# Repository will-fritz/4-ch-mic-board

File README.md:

# 4-ch-mic-board
4 ch microphone board to replace seed studio 6 ch microphone board stack

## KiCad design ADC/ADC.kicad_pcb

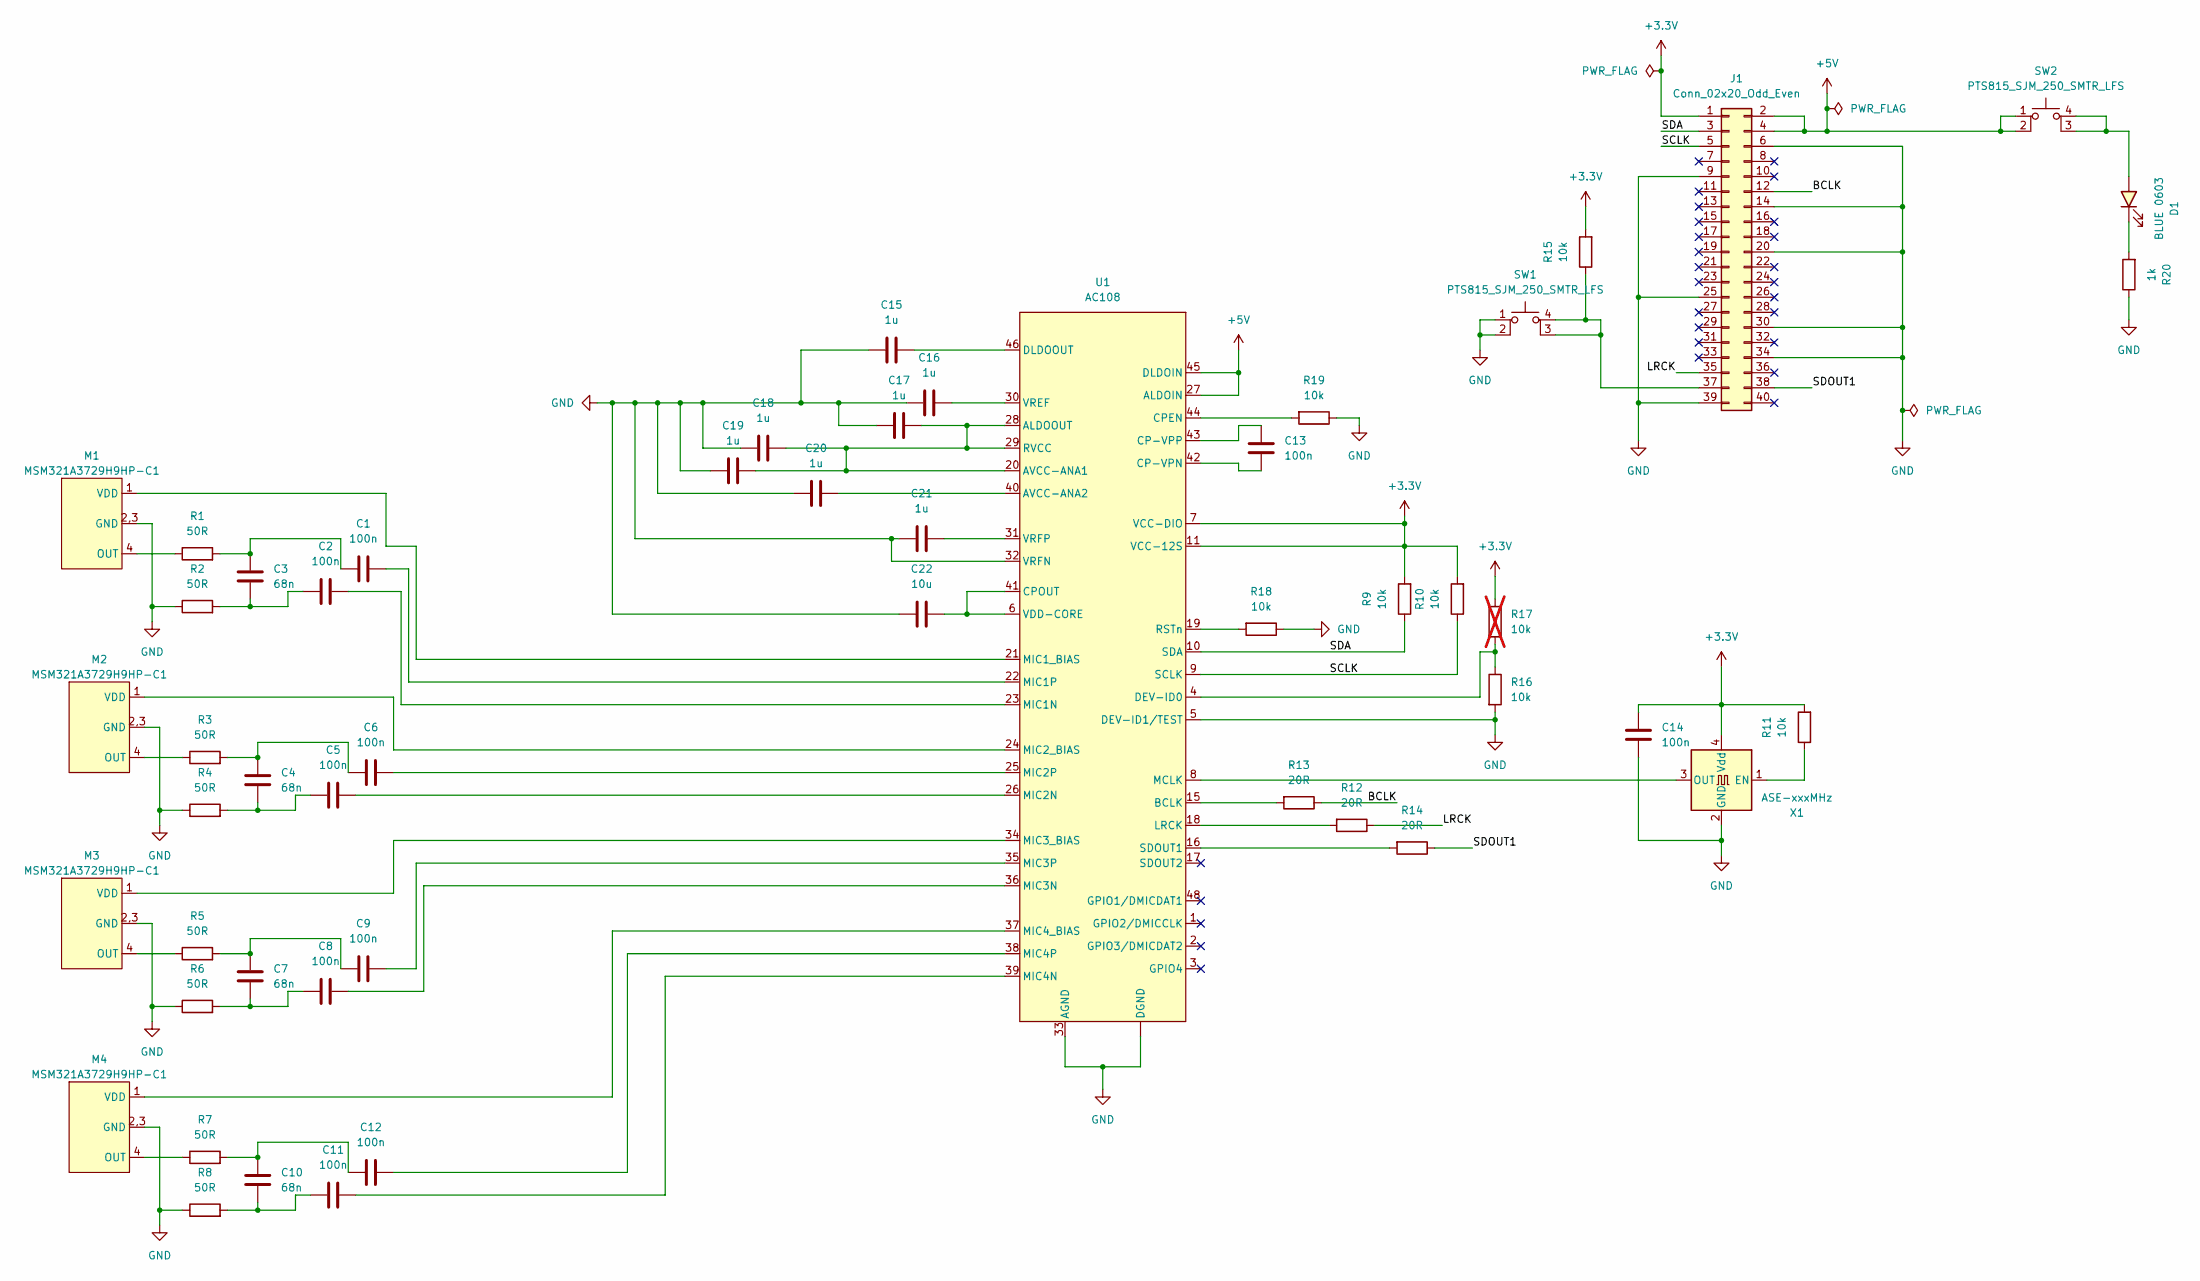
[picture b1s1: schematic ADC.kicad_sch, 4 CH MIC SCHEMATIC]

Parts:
C1, C2, C5, C6, C8, C9, C11, C12, C13, C14: 100n; C_0603_1608Metric
C3, C4, C7, C10: 68n; C_0603_1608Metric
C15, C16, C17, C18, C19, C20, C21: 1u; C_0603_1608Metric
C22: 10u; C_0603_1608Metric
D1: BLUE 0603; LED_0603_1608Metric; MPN EAST16084BA0
J1: Conn_02x20_Odd_Even; PinSocket_2x20_P2.54mm_Vertical
M1, M2, M3, M4: MSM321A3729H9HP-C1; MSM321A3729H8HP-C_FP
R1, R2, R3, R4, R5, R6, R7, R8: 50R; R_0603_1608Metric
R9, R10, R11, R15, R16, R18, R19: 10k; R_0603_1608Metric
R12, R13, R14: 20R; R_0603_1608Metric
R17: 10k; R_0603_1608Metric; not fitted
R20: 1k; R_0603_1608Metric
SW1, SW2: PTS815_SJM_250_SMTR_LFS; MPN PTS815 SJM 250 SMTR LFS
U1: AC108
X1: ASE-xxxMHz; Oscillator_SMD_Abracon_ASE-4Pin_3.2x2.5mm

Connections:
+3.3V: C14.2, J1.1, R9.2, R10.2, R11.2, R15.2, R17.1, U1.7 (VCC-DIO), U1.11 (VCC-12S), X1.4 (Vdd)
+5V: J1.2, J1.4, SW2.1, SW2.2, U1.27 (ALDOIN), U1.45 (DLDOIN)
/BCLK: J1.12, R13.1
/LRCK: J1.35, R12.1
/SCLK: J1.5, R10.1, U1.9 (SCLK)
/SDA: J1.3, R9.1, U1.10 (SDA)
/SDOUT1: J1.38, R14.1
GND: C14.1, C15.1, C16.1, C17.1, C18.1, C19.1, C20.1, C21.1, C22.1, J1.6, J1.9, J1.14, J1.20, J1.25, J1.30, J1.34, J1.39, M1.2, M1.2,3 (GND), M1.3, M2.2, M2.2,3 (GND), M2.3, M3.2, M3.2,3 (GND), M3.3, M4.2, M4.2,3 (GND), M4.3, R2.1, R4.1, R6.1, R8.1, R16.2, R18.1, R19.1, R20.1, SW1.1, SW1.2, U1. (DGND), U1.5 (DEV-ID1/TEST), U1.32 (VRFN), U1.33 (AGND), X1.2 (GND)
unnamed: C1.1, C3.1, R1.2
unnamed: C2.1, C3.2, R2.2
unnamed: C4.1, C6.1, R3.2
unnamed: C4.2, C5.1, R4.2
unnamed: C7.1, C9.1, R5.2
unnamed: C7.2, C8.1, R6.2
unnamed: C10.1, C12.1, R7.2
unnamed: C10.2, C11.1, R8.2
unnamed: D1.2 (A), SW2.3 (K), SW2.4 (A)
unnamed: D1.1 (K), R20.2
unnamed: J1.37, R15.1, SW1.3 (K), SW1.4 (A)
unnamed: M1.4 (OUT), R1.1
unnamed: M1.1 (VDD), U1.21 (MIC1_BIAS)
unnamed: M2.4 (OUT), R3.1
unnamed: M2.1 (VDD), U1.24 (MIC2_BIAS)
unnamed: M3.4 (OUT), R5.1
unnamed: M3.1 (VDD), U1.34 (MIC3_BIAS)
unnamed: M4.4 (OUT), R7.1
unnamed: M4.1 (VDD), U1.37 (MIC4_BIAS)
unnamed: C17.2, C18.2, C19.2, U1.20 (AVCC-ANA1), U1.28 (ALDOOUT), U1.29 (RVCC)
unnamed: C20.2, U1.40 (AVCC-ANA2)
unnamed: R13.2, U1.15 (BCLK)
unnamed: C13.1, U1.42 (CP-VPN)
unnamed: C13.2, U1.43 (CP-VPP)
unnamed: R19.2, U1.44 (CPEN)
unnamed: C22.2, U1.6 (VDD-CORE), U1.41 (CPOUT)
unnamed: R16.1, R17.2, U1.4 (DEV-ID0)
unnamed: C15.2, U1.46 (DLDOOUT)
unnamed: R12.2, U1.18 (LRCK)
unnamed: U1.8 (MCLK), X1.3 (OUT)
unnamed: C2.2, U1.23 (MIC1N)
unnamed: C1.2, U1.22 (MIC1P)
unnamed: C5.2, U1.26 (MIC2N)
unnamed: C6.2, U1.25 (MIC2P)
unnamed: C8.2, U1.36 (MIC3N)
unnamed: C9.2, U1.35 (MIC3P)
unnamed: C11.2, U1.39 (MIC4N)
unnamed: C12.2, U1.38 (MIC4P)
unnamed: R18.2, U1.19 (RSTn)
unnamed: R14.2, U1.16 (SDOUT1)
unnamed: C16.2, U1.30 (VREF)
unnamed: C21.2, U1.31 (VRFP)
unnamed: R11.1, X1.1 (EN)

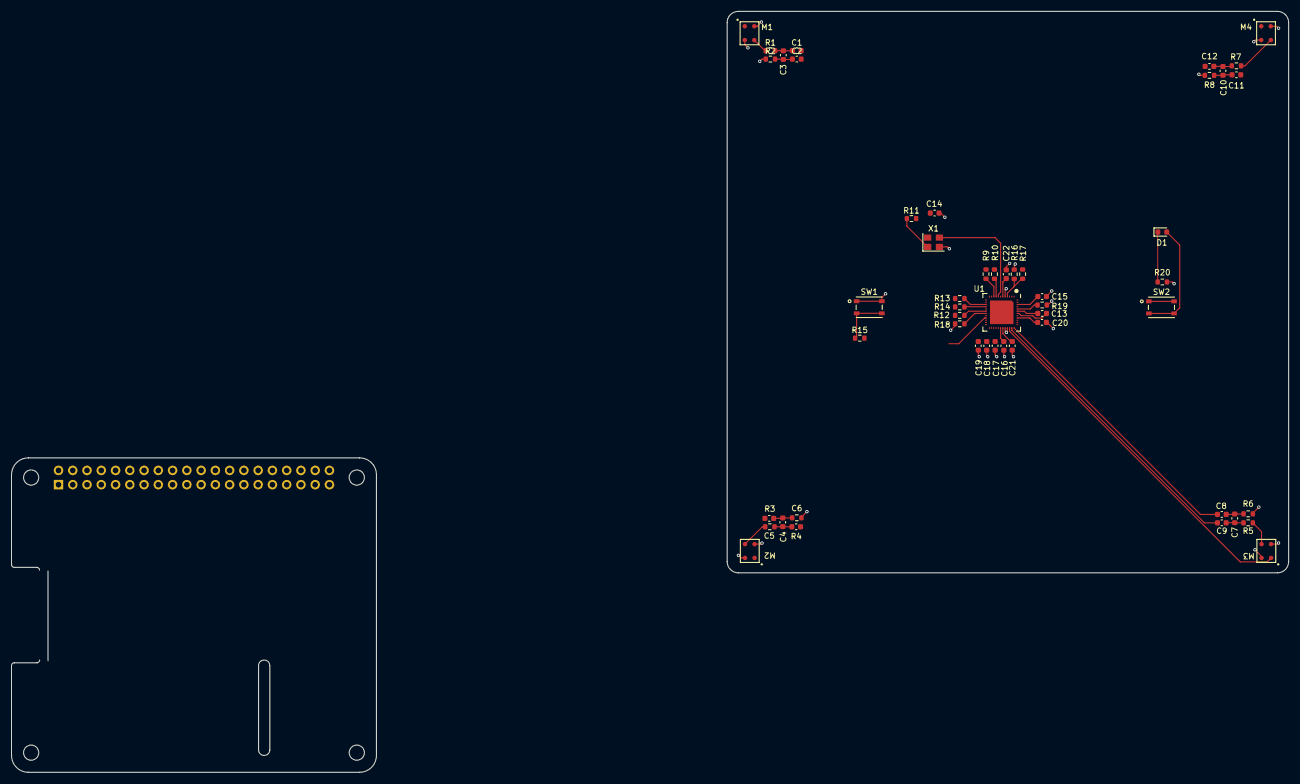
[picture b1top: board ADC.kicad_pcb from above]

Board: 4 copper layers, 227.4 x 135.5 mm, 56 parts (1 on the bottom side), 51 nets.

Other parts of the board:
MH1, MH2, MH3, MH4: MountingHole_2.7mm_M2.5

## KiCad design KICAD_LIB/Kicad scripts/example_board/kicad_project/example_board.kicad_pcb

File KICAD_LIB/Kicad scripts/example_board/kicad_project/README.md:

# KiCad project to use as demo for python scripts

## This board is intended for demo purposes only, it is not meant to be manufactured

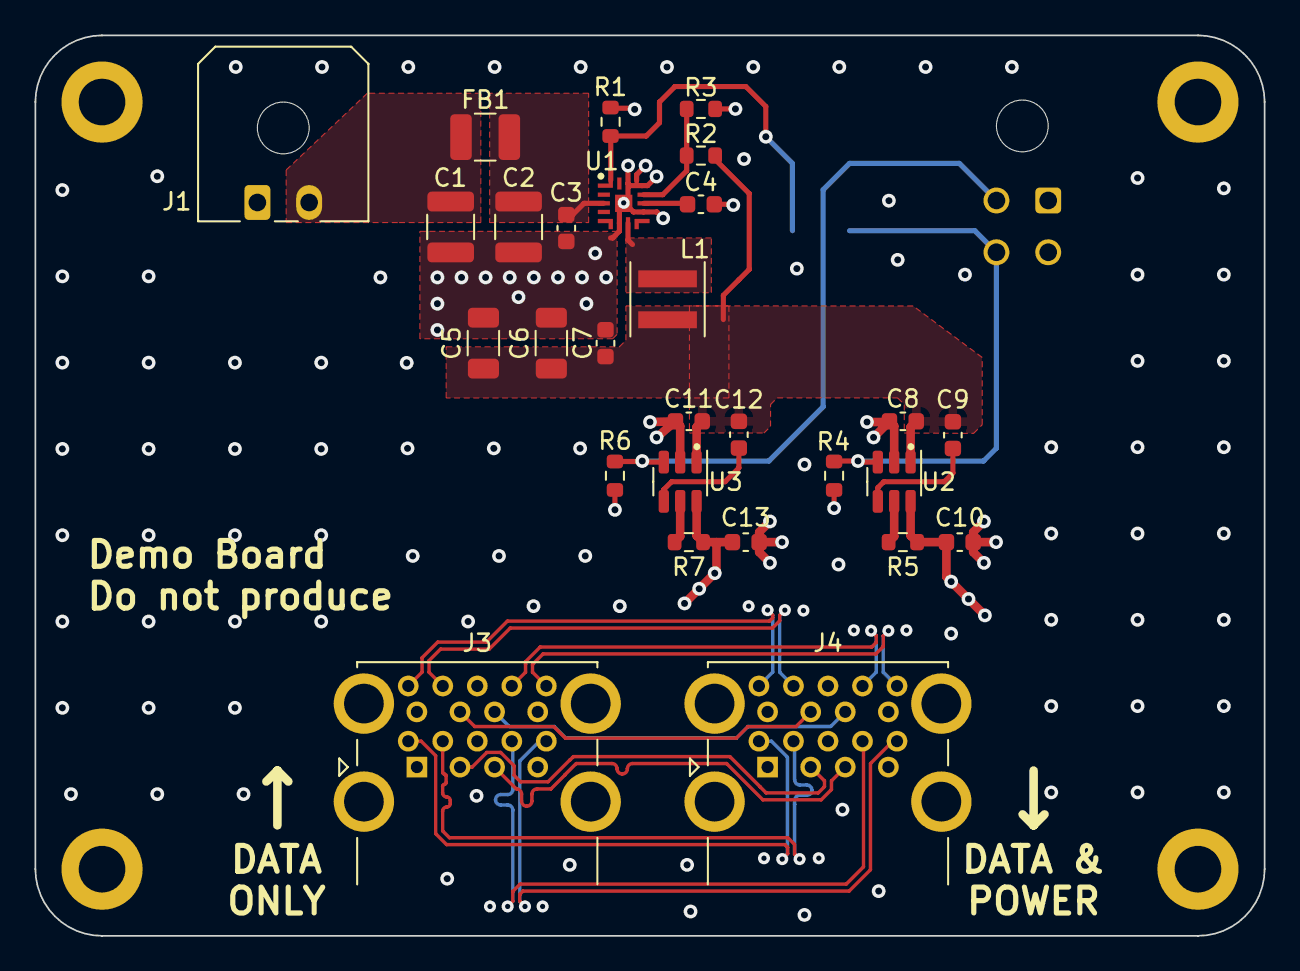
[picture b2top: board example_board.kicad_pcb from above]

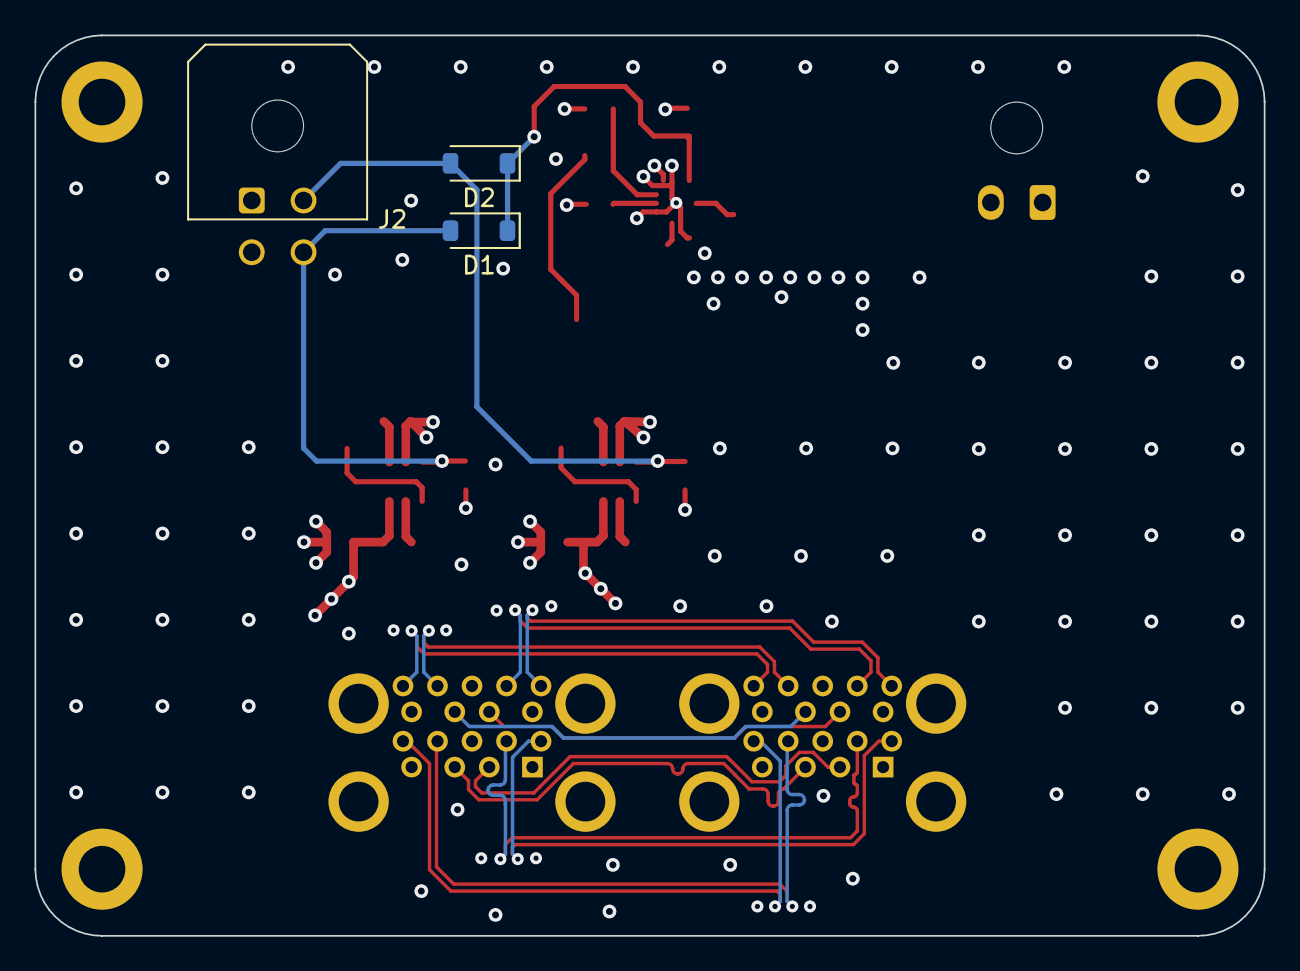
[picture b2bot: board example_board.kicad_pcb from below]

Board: 4 copper layers, 71.2 x 52.2 mm, 35 parts (3 on the bottom side), 28 nets.

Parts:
C1, C2: 10u 50V; C_1210_3225Metric
C3: 100n 50v; C_0603_1608Metric
C4, C8, C10, C11, C13: 1u 50V; C_0603_1608Metric
C5, C6: 22u 10v; C_1206_3216Metric
C7: 100n 25v; C_0603_1608Metric
C9, C12: 470p; C_0603_1608Metric
D1, D2: 1N4148W; D_SOD-123
FB1: 1k @100MHz 2A; L_1210_3225Metric
H1, H2, H3, H4: MountingHole_Pad; MountingHole_2.7mm_M2.5_DIN965_Pad
J1: micro-fit_1x2_3mm; Molex_Micro-Fit_3.0_43650-0200_1x02_P3.00mm_Horizontal
J2: micro-fit_2x2_3mm; Molex_Micro-Fit_3.0_43045-0400_2x02_P3.00mm_Horizontal
J3, J4: molex_048406-0001; USB3_A_Molex_48406-0001_Horizontal_Stacked
L1: 3u3 5A; L_Coilcraft_XxL4030
R1, R4, R6: 1M; R_0603_1608Metric
R2: 0R; R_0603_1608Metric
R3: DNF; R_0603_1608Metric
R5, R7: 10k; R_0603_1608Metric
U1: LMQ66430R5RXBR; VQFN-FCRLF14_RXB_TEX
U2, U3: TPS22917DBVx; SOT-23-6

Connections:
+5V: C5.1, C6.1, C7.1, C8.1, C9.1, C11.1, C12.1, L1.2, R2.1, U2.1 (IN), U3.1 (IN)
/USB_in/USB_btm_data.D+: J3.3 (D1+), J4.3 (D1+)
/USB_in/USB_btm_data.D-: J3.2 (D1-), J4.2 (D1-)
/USB_in/USB_btm_data.SSRX+: J3.6 (SSRX1+), J4.6 (SSRX1+)
/USB_in/USB_btm_data.SSRX-: J3.5 (SSRX1-), J4.5 (SSRX1-)
/USB_in/USB_btm_data.SSTX+: J3.9 (SSTX1+), J4.9 (SSTX1+)
/USB_in/USB_btm_data.SSTX-: J3.8 (SSTX1-), J4.8 (SSTX1-)
/USB_in/USB_top_data.D+: J3.12 (D2+), J4.12 (D2+)
/USB_in/USB_top_data.D-: J3.11 (D2-), J4.11 (D2-)
/USB_in/USB_top_data.SSRX+: J3.15 (SSRX2+), J4.15 (SSRX2+)
/USB_in/USB_top_data.SSRX-: J3.14 (SSRX2-), J4.14 (SSRX2-)
/USB_in/USB_top_data.SSTX+: J3.18 (SSTX2+), J4.18 (SSTX2+)
/USB_in/USB_top_data.SSTX-: J3.17 (SSTX2-), J4.17 (SSTX2-)
/USB_out/VBUS_BTM: C13.1, J4.1 (VBUS1), R7.1, U3.6 (OUT)
/USB_out/VBUS_TOP: C10.1, J4.10 (VBUS2), R5.1, U2.6 (OUT)
/power_ctl/FB: R2.2, R3.1, U1.11 (VOUT/FB)
/power_ctl/REG_EN: D1.1 (K), D2.1 (K), R1.1, U1.1 (EN)
/power_ctl/SW: L1.1, U1.7 (SW)
/power_ctl/VBUS_BTM_EN: D2.2 (A), J2.2, R6.1, U3.3 (ON)
/power_ctl/VBUS_TOP_EN: D1.2 (A), J2.4, R4.1, U2.3 (ON)
/power_ctl/VIN: C1.1, FB1.2, J1.2
/power_ctl/VIN_FILT: C2.1, C3.1, FB1.1, U1.3 (VIN)
GND: C1.2, C2.2, C3.2, C4.2, C5.2, C6.2, C7.2, C8.2, C10.2, C11.2, C13.2, H1.1, H2.1, H3.1, H4.1, J1.1, J2.1, J2.3, J3.4 (GND1), J3.7 (DRAIN1), J3.13 (GND2), J3.16 (DRAIN2), J3.19 (SHIELD), J4.4 (GND1), J4.7 (DRAIN1), J4.13 (GND2), J4.16 (DRAIN2), J4.19 (SHIELD), R1.2, R3.2, R4.2, R6.2, U1.6 (PGND), U1.9 (FREE), U1.12 (FREE), U1.13 (RT), U1.15 (GND), U2.2 (GND), U3.2 (GND)
unnamed: C4.1, U1.10 (VCC)
unnamed: C9.2, U2.4 (CT)
unnamed: R5.2, U2.5 (QOD)
unnamed: C12.2, U3.4 (CT)
unnamed: R7.2, U3.5 (QOD)

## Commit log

2024-08-07 Initial commit of ADC symboles and footprint kicad 8.0
2024-08-07 Added pin 1 marker to ADC
2024-08-08 Added symbols and footprints for Kicad
2024-08-20 Updated KiCAD library to CCB standard. Added reverse engineering document files.
2024-08-28 Added SVG drawings and datasheets
2024-08-28 Composite circuit document
2024-08-30 Added replacement mic datasheet and project presentation. Cleaned up documents.
2024-08-30 Initial schematic completed
2024-09-04 New layout for Mics
